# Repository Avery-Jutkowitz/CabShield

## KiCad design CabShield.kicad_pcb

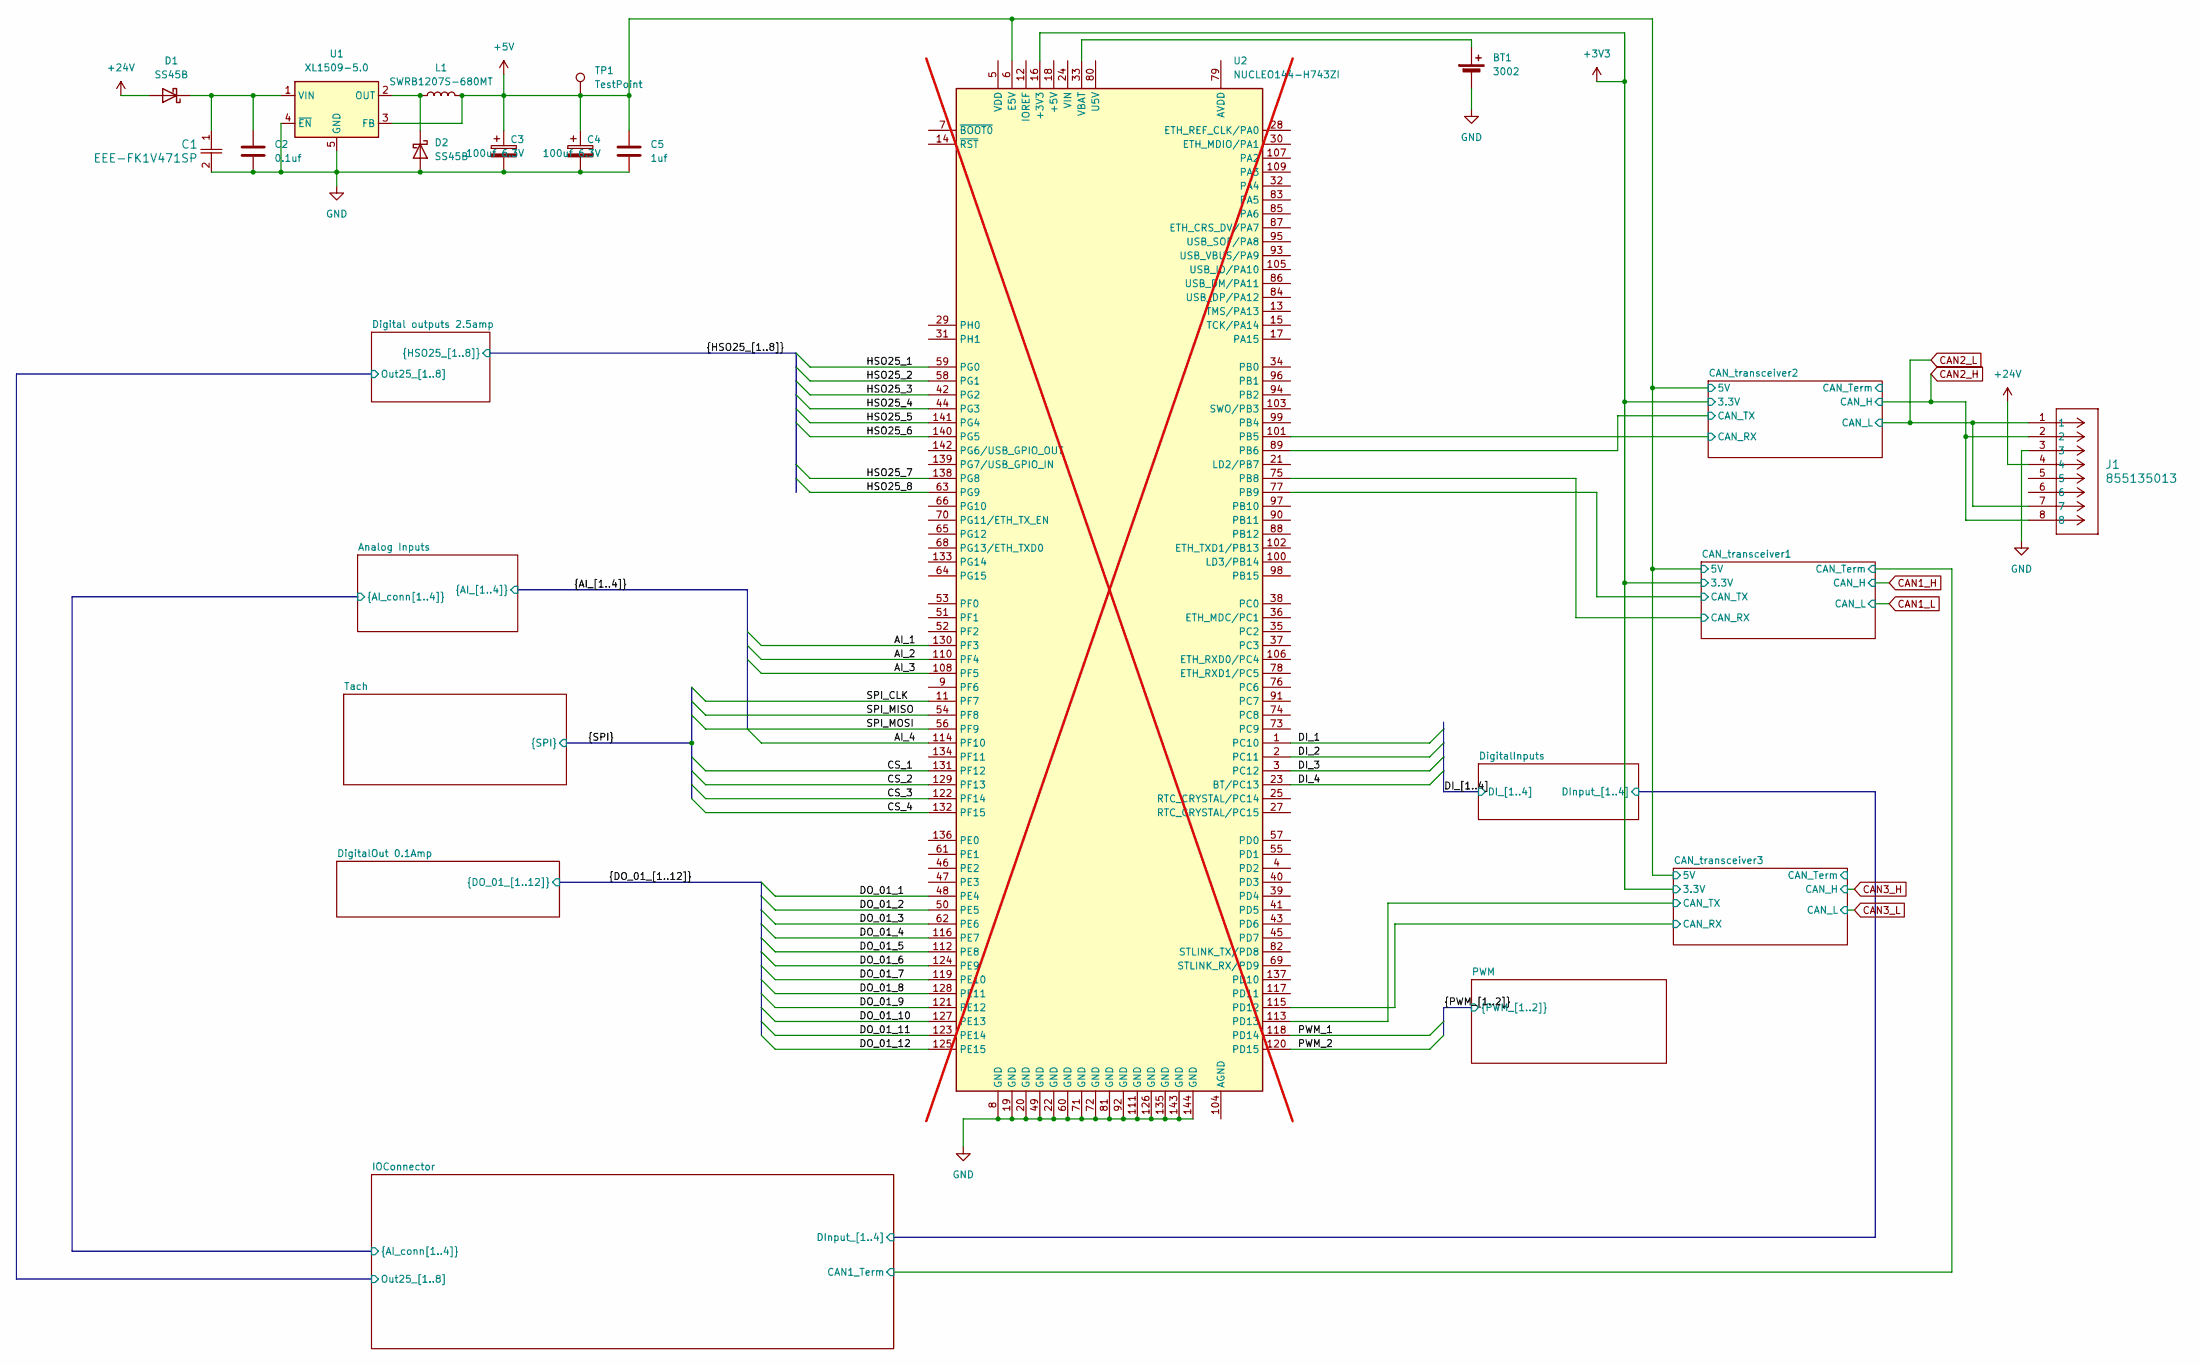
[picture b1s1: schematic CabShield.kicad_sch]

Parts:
BT1: 3002; BatteryHolder_Keystone_3002_1x2032; Manufacturer_Part_Number 3002
C1: EEE-FK1V471SP; CAP_FKS_G_PAN; Manufacturer_Part_Number EEE-FK1V471SP
C2: 0.1uf; C_0603_1608Metric; Manufacturer_Part_Number 0603B104K500XD
C3, C4: 100uf 6.3V; C_1210_3225Metric; Manufacturer_Part_Number TAJB107K006RNJ
C5: 1uf; C_0603_1608Metric; Manufacturer_Part_Number 0603B105K500XD
D1, D2: SS45B; D_SMB; Manufacturer_Part_Number SS45B
J1: 855135013; CONN_85513-5013_MOL; Manufacturer_Part_Number 855135013
L1: SWRB1207S-680MT; L_Sunlord_SWRB1204S; Manufacturer_Part_Number SWRB1207S-680MT
TP1: TestPoint; TestPoint_Pad_1.5x1.5mm
U1: XL1509-5.0; SOIC-8_3.9x4.9mm_P1.27mm; Manufacturer_Part_Number XL1509-5.0
U2: NUCLEO144-H743ZI; ST_Morpho_Connector_144_STLink; not fitted

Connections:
+3V3: U2.16 (+3V3); also elsewhere on the board
+5V: C3.1, C4.1, C5.1, L1.2, TP1.1, U1.3 (FB), U2.6 (E5V); also elsewhere on the board
+24V: D1.2 (A), J1.4; also elsewhere on the board
/AI_1: U2.130 (PF3); also elsewhere on the board
/AI_2: U2.110 (PF4); also elsewhere on the board
/AI_3: U2.108 (PF5); also elsewhere on the board
/AI_4: U2.114 (PF10); also elsewhere on the board
/CAN_transceiver1/CAN_RX: U2.75 (PB8); also elsewhere on the board
/CAN_transceiver1/CAN_TX: U2.77 (PB9); also elsewhere on the board
/CAN_transceiver2/CAN_H: J1.2, J1.8; also elsewhere on the board
/CAN_transceiver2/CAN_L: J1.1, J1.7; also elsewhere on the board
/CAN_transceiver2/CAN_RX: U2.101 (PB5); also elsewhere on the board
/CAN_transceiver2/CAN_TX: U2.89 (PB6); also elsewhere on the board
/CS_1: U2.131 (PF12); also elsewhere on the board
/CS_2: U2.129 (PF13); also elsewhere on the board
/CS_3: U2.122 (PF14); also elsewhere on the board
/CS_4: U2.132 (PF15); also elsewhere on the board
/DI_1: U2.1 (PC10); also elsewhere on the board
/DI_2: U2.2 (PC11); also elsewhere on the board
/DI_3: U2.3 (PC12); also elsewhere on the board
/DI_4: U2.23 (BT/PC13); also elsewhere on the board
/DO_01_1: U2.48 (PE4); also elsewhere on the board
/DO_01_2: U2.50 (PE5); also elsewhere on the board
/DO_01_3: U2.62 (PE6); also elsewhere on the board
/DO_01_4: U2.116 (PE7); also elsewhere on the board
/DO_01_5: U2.112 (PE8); also elsewhere on the board
/DO_01_6: U2.124 (PE9); also elsewhere on the board
/DO_01_7: U2.119 (PE10); also elsewhere on the board
/DO_01_8: U2.128 (PE11); also elsewhere on the board
/DO_01_9: U2.121 (PE12); also elsewhere on the board
/DO_01_10: U2.127 (PE13); also elsewhere on the board
/DO_01_11: U2.123 (PE14); also elsewhere on the board
/DO_01_12: U2.125 (PE15); also elsewhere on the board
/HSO25_1: U2.59 (PG0); also elsewhere on the board
/HSO25_2: U2.58 (PG1); also elsewhere on the board
/HSO25_3: U2.42 (PG2); also elsewhere on the board
/HSO25_4: U2.44 (PG3); also elsewhere on the board
/HSO25_5: U2.141 (PG4); also elsewhere on the board
/HSO25_6: U2.140 (PG5); also elsewhere on the board
/HSO25_7: U2.138 (PG8); also elsewhere on the board
/HSO25_8: U2.63 (PG9); also elsewhere on the board
/PWM_1: U2.118 (PD14); also elsewhere on the board
/PWM_2: U2.120 (PD15); also elsewhere on the board
/SPI_CLK: U2.11 (PF7); also elsewhere on the board
/SPI_MISO: U2.54 (PF8); also elsewhere on the board
/SPI_MOSI: U2.56 (PF9); also elsewhere on the board
GND: BT1.2 (-), C1.2, C2.2, C3.2, C4.2, C5.2, D2.2 (A), J1.3, U1.4 (~EN), U1.5 (GND), U1.6 (GND), U1.7 (GND), U1.8 (GND), U2.8 (GND), U2.19 (GND), U2.20 (GND), U2.22 (GND), U2.49 (GND), U2.60 (GND), U2.71 (GND), U2.72 (GND), U2.81 (GND), U2.92 (GND), U2.111 (GND), U2.126 (GND), U2.135 (GND), U2.143 (GND), U2.144 (GND); also elsewhere on the board
unnamed: BT1.1 (+), U2.33 (VBAT)
unnamed: C1.1, C2.1, D1.1 (K), U1.1 (VIN)
unnamed: D2.1 (K), L1.1, U1.2 (OUT)

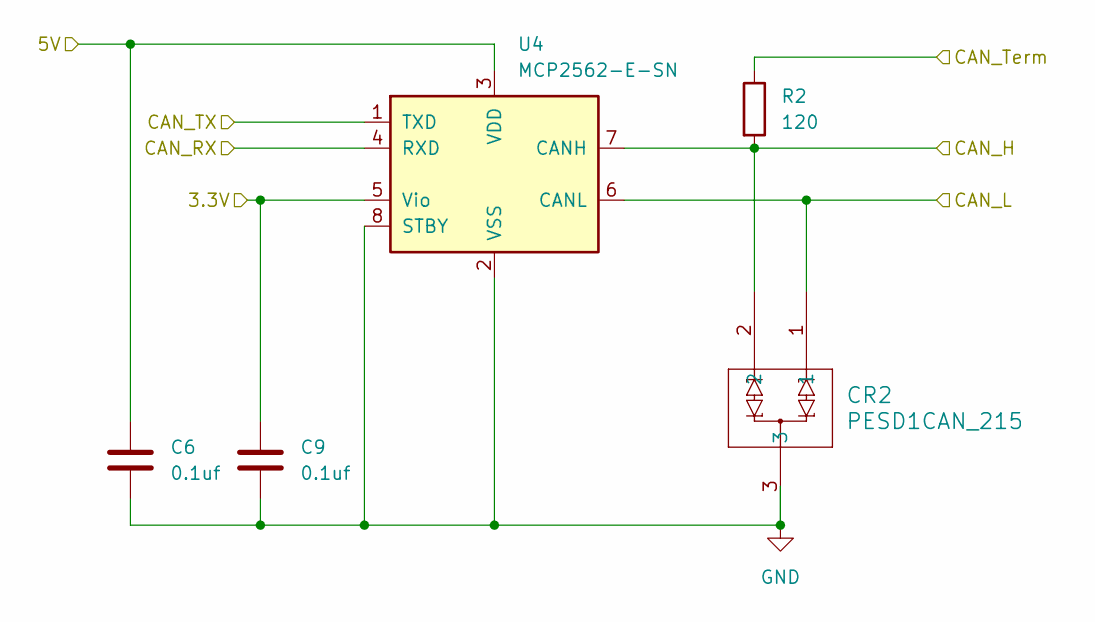
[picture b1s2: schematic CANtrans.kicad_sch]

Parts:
C6, C9: 0.1uf; C_0603_1608Metric; Manufacturer_Part_Number 0603B104K500XD
CR2: PESD1CAN_215; SOT-23; Manufacturer_Part_Number PESD1CAN_215
R2: 120; R_0603_1608Metric_Pad0.98x0.95mm_HandSolder; Manufacturer_Part_Number ERJ-3EKF1200V
U4: MCP2562-E-SN; SOIC-8_3.9x4.9mm_P1.27mm; Manufacturer_Part_Number MCP2562-E-SN

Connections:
+3V3: C9.1, U4.5 (Vio); also elsewhere on the board
+5V: C6.1, U4.3 (VDD); also elsewhere on the board
/CAN_transceiver2/CAN_H: CR2.2, R2.2, U4.7 (CANH); also elsewhere on the board
/CAN_transceiver2/CAN_L: CR2.1, U4.6 (CANL); also elsewhere on the board
/CAN_transceiver2/CAN_RX: U4.4 (RXD); also elsewhere on the board
/CAN_transceiver2/CAN_TX: U4.1 (TXD); also elsewhere on the board
/CAN_transceiver2/CAN_Term: R2.1
GND: C6.2, C9.2, CR2.3, U4.2 (VSS), U4.8 (STBY); also elsewhere on the board

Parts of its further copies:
C7, C8: 0.1uf; C_0603_1608Metric; Manufacturer_Part_Number 0603B104K500XD
CR1: PESD1CAN_215; SOT-23; Manufacturer_Part_Number PESD1CAN_215
R1: 120; R_0603_1608Metric_Pad0.98x0.95mm_HandSolder; Manufacturer_Part_Number ERJ-3EKF1200V
U3: MCP2562-E-SN; SOIC-8_3.9x4.9mm_P1.27mm; Manufacturer_Part_Number MCP2562-E-SN

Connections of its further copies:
+3V3: C7.1, U3.5 (Vio); also elsewhere on the board
+5V: C8.1, U3.3 (VDD); also elsewhere on the board
/CAN_transceiver1/CAN_RX: U3.4 (RXD); also elsewhere on the board
/CAN_transceiver1/CAN_TX: U3.1 (TXD); also elsewhere on the board
/CAN_transceiver1/CAN_Term: R1.1; also elsewhere on the board
GND: C7.2, C8.2, CR1.3, U3.2 (VSS), U3.8 (STBY); also elsewhere on the board

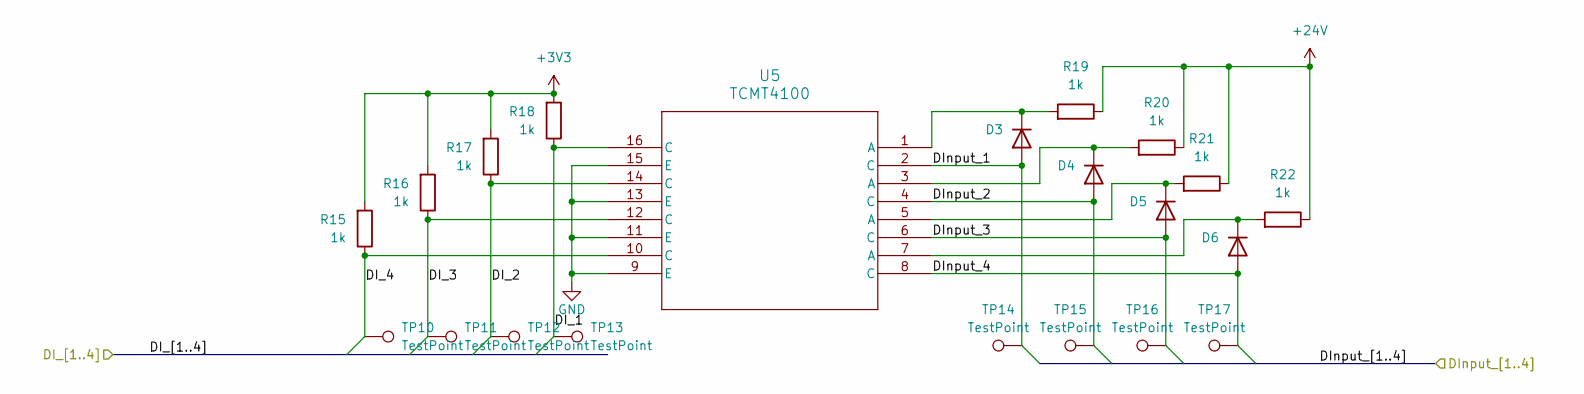
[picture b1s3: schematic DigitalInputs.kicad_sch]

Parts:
D3, D4, D5, D6: MMSZ5222BT1G; D_SOD-123; Manufacturer_Part_Number MMSZ5222BT1G
R15, R16, R17, R18, R19, R20, R21, R22: 1k; R_0402_1005Metric_Pad0.72x0.64mm_HandSolder; Manufacturer_Part_Number ERJ-2GEJ102X
TP10, TP11, TP12, TP13, TP14, TP15, TP16, TP17: TestPoint; TestPoint_Pad_1.5x1.5mm
U5: TCMT4100; SOP-16_TCMT_VIS; Manufacturer_Part_Number TCMT4100

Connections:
+3V3: R15.2, R16.2, R17.2, R18.2; also elsewhere on the board
+24V: R19.1, R20.1, R21.1, R22.1; also elsewhere on the board
/DI_1: R18.1, TP13.1, U5.16 (C); also elsewhere on the board
/DI_2: R17.1, TP12.1, U5.14 (C); also elsewhere on the board
/DI_3: R16.1, TP11.1, U5.12 (C); also elsewhere on the board
/DI_4: R15.1, TP10.1, U5.10 (C); also elsewhere on the board
/DigitalInputs/DInput_1: D3.2 (A), TP14.1, U5.2 (C); also elsewhere on the board
/DigitalInputs/DInput_2: D4.2 (A), TP15.1, U5.4 (C); also elsewhere on the board
/DigitalInputs/DInput_3: D5.2 (A), TP16.1, U5.6 (C); also elsewhere on the board
/DigitalInputs/DInput_4: D6.2 (A), TP17.1, U5.8 (C); also elsewhere on the board
GND: U5.9 (E), U5.11 (E), U5.13 (E), U5.15 (E); also elsewhere on the board
unnamed: D3.1 (K), R19.2, U5.1 (A)
unnamed: D4.1 (K), R20.2, U5.3 (A)
unnamed: D5.1 (K), R21.2, U5.5 (A)
unnamed: D6.1 (K), R22.2, U5.7 (A)

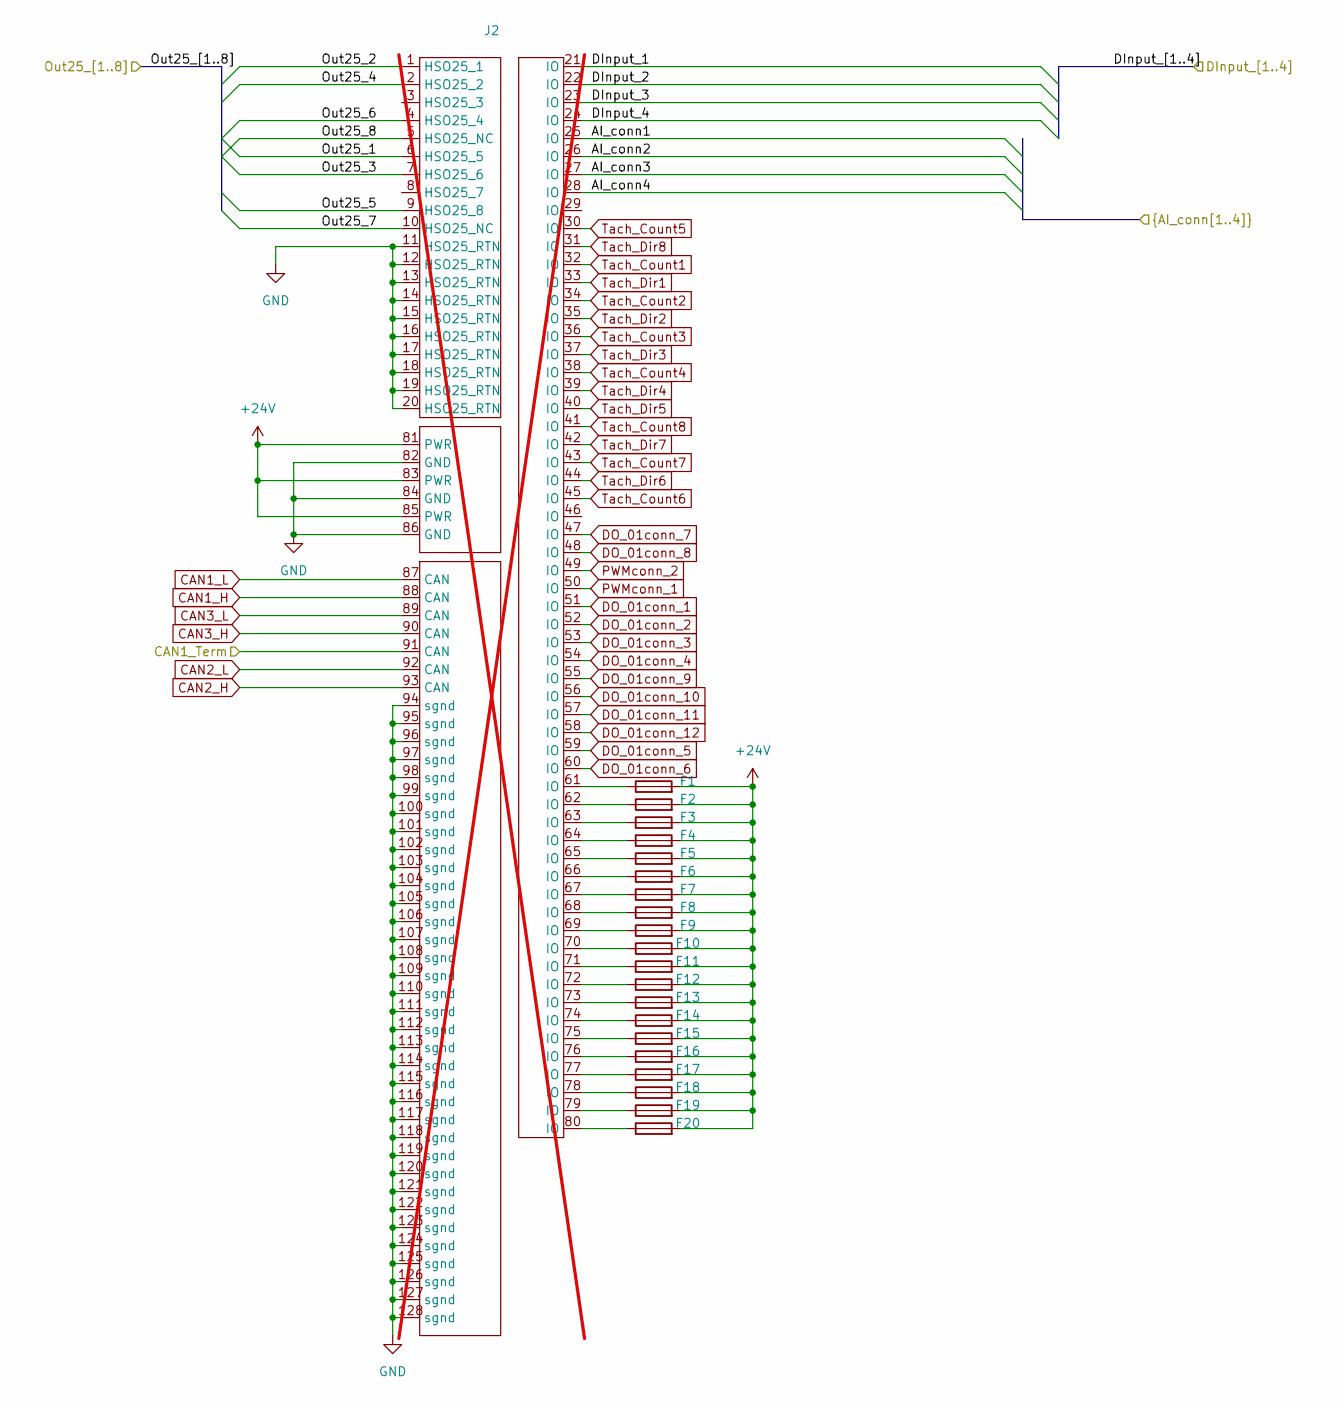
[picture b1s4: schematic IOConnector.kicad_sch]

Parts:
F1, F2, F3, F4, F5, F6, F7, F8, F9, F10, F11, F12, F13, F14, F15, F16, F17, F18, F19, F20: MF-MSMF030; Fuse_2920_7451Metric_Pad2.10x5.45mm_HandSolder; Manufacturer_Part_Number MF-MSMF030
J2: Compactus128; not fitted

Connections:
+24V: F1.2, F2.2, F3.2, F4.2, F5.2, F6.2, F7.2, F8.2, F9.2, F10.2, F11.2, F12.2, F13.2, F14.2, F15.2, F16.2, F17.2, F18.2, F19.2, F20.2, J2.81 (PWR), J2.83 (PWR), J2.85 (PWR); also elsewhere on the board
/Analog Inputs/AI_conn1: J2.25 (IO); also elsewhere on the board
/Analog Inputs/AI_conn2: J2.26 (IO); also elsewhere on the board
/Analog Inputs/AI_conn3: J2.27 (IO); also elsewhere on the board
/Analog Inputs/AI_conn4: J2.28 (IO); also elsewhere on the board
/CAN_transceiver1/CAN_Term: J2.91 (CAN); also elsewhere on the board
/CAN_transceiver2/CAN_H: J2.93 (CAN); also elsewhere on the board
/CAN_transceiver2/CAN_L: J2.92 (CAN); also elsewhere on the board
/DigitalInputs/DInput_1: J2.21 (IO); also elsewhere on the board
/DigitalInputs/DInput_2: J2.22 (IO); also elsewhere on the board
/DigitalInputs/DInput_3: J2.23 (IO); also elsewhere on the board
/DigitalInputs/DInput_4: J2.24 (IO); also elsewhere on the board
/IOConnector/Out25_1: J2.6 (HSO25_5); also elsewhere on the board
/IOConnector/Out25_2: J2.1 (HSO25_1); also elsewhere on the board
/IOConnector/Out25_3: J2.7 (HSO25_6); also elsewhere on the board
/IOConnector/Out25_4: J2.2 (HSO25_2); also elsewhere on the board
/IOConnector/Out25_5: J2.9 (HSO25_8); also elsewhere on the board
/IOConnector/Out25_6: J2.4 (HSO25_4); also elsewhere on the board
/IOConnector/Out25_7: J2.10 (HSO25_NC); also elsewhere on the board
/IOConnector/Out25_8: J2.5 (HSO25_NC); also elsewhere on the board
DO_01conn_1: J2.51 (IO); also elsewhere on the board
DO_01conn_2: J2.52 (IO); also elsewhere on the board
DO_01conn_3: J2.53 (IO); also elsewhere on the board
DO_01conn_4: J2.54 (IO); also elsewhere on the board
DO_01conn_5: J2.59 (IO); also elsewhere on the board
DO_01conn_6: J2.60 (IO); also elsewhere on the board
DO_01conn_7: J2.47 (IO); also elsewhere on the board
DO_01conn_8: J2.48 (IO); also elsewhere on the board
DO_01conn_9: J2.55 (IO); also elsewhere on the board
DO_01conn_10: J2.56 (IO); also elsewhere on the board
DO_01conn_11: J2.57 (IO); also elsewhere on the board
DO_01conn_12: J2.58 (IO); also elsewhere on the board
GND: J2.11 (HSO25_RTN), J2.12 (HSO25_RTN), J2.13 (HSO25_RTN), J2.14 (HSO25_RTN), J2.15 (HSO25_RTN), J2.16 (HSO25_RTN), J2.17 (HSO25_RTN), J2.18 (HSO25_RTN), J2.19 (HSO25_RTN), J2.20 (HSO25_RTN), J2.82 (GND), J2.84 (GND), J2.86 (GND), J2.94 (sgnd), J2.95 (sgnd), J2.96 (sgnd), J2.97 (sgnd), J2.98 (sgnd), J2.99 (sgnd), J2.100 (sgnd), J2.101 (sgnd), J2.102 (sgnd), J2.103 (sgnd), J2.104 (sgnd), J2.105 (sgnd), J2.106 (sgnd), J2.107 (sgnd), J2.108 (sgnd), J2.109 (sgnd), J2.110 (sgnd), J2.111 (sgnd), J2.112 (sgnd), J2.113 (sgnd), J2.114 (sgnd), J2.115 (sgnd), J2.116 (sgnd), J2.117 (sgnd), J2.118 (sgnd), J2.119 (sgnd), J2.120 (sgnd), J2.121 (sgnd), J2.122 (sgnd), J2.123 (sgnd), J2.124 (sgnd), J2.125 (sgnd), J2.126 (sgnd), J2.127 (sgnd), J2.128 (sgnd); also elsewhere on the board
unnamed: F1.1, J2.61 (IO)
unnamed: F2.1, J2.62 (IO)
unnamed: F3.1, J2.63 (IO)
unnamed: F4.1, J2.64 (IO)
unnamed: F5.1, J2.65 (IO)
unnamed: F6.1, J2.66 (IO)
unnamed: F7.1, J2.67 (IO)
unnamed: F8.1, J2.68 (IO)
unnamed: F9.1, J2.69 (IO)
unnamed: F10.1, J2.70 (IO)
unnamed: F11.1, J2.71 (IO)
unnamed: F12.1, J2.72 (IO)
unnamed: F13.1, J2.73 (IO)
unnamed: F14.1, J2.74 (IO)
unnamed: F15.1, J2.75 (IO)
unnamed: F16.1, J2.76 (IO)
unnamed: F17.1, J2.77 (IO)
unnamed: F18.1, J2.78 (IO)
unnamed: F19.1, J2.79 (IO)
unnamed: F20.1, J2.80 (IO)
PWMconn_1: J2.50 (IO); also elsewhere on the board
PWMconn_2: J2.49 (IO); also elsewhere on the board
Tach_Count1: J2.32 (IO); also elsewhere on the board
Tach_Count2: J2.34 (IO); also elsewhere on the board
Tach_Count3: J2.36 (IO); also elsewhere on the board
Tach_Count4: J2.38 (IO); also elsewhere on the board
Tach_Count5: J2.30 (IO); also elsewhere on the board
Tach_Count6: J2.45 (IO); also elsewhere on the board
Tach_Count7: J2.43 (IO); also elsewhere on the board
Tach_Count8: J2.41 (IO); also elsewhere on the board
Tach_Dir1: J2.33 (IO); also elsewhere on the board
Tach_Dir2: J2.35 (IO); also elsewhere on the board
Tach_Dir3: J2.37 (IO); also elsewhere on the board
Tach_Dir4: J2.39 (IO); also elsewhere on the board
Tach_Dir5: J2.40 (IO); also elsewhere on the board
Tach_Dir6: J2.44 (IO); also elsewhere on the board
Tach_Dir7: J2.42 (IO); also elsewhere on the board
Tach_Dir8: J2.31 (IO); also elsewhere on the board

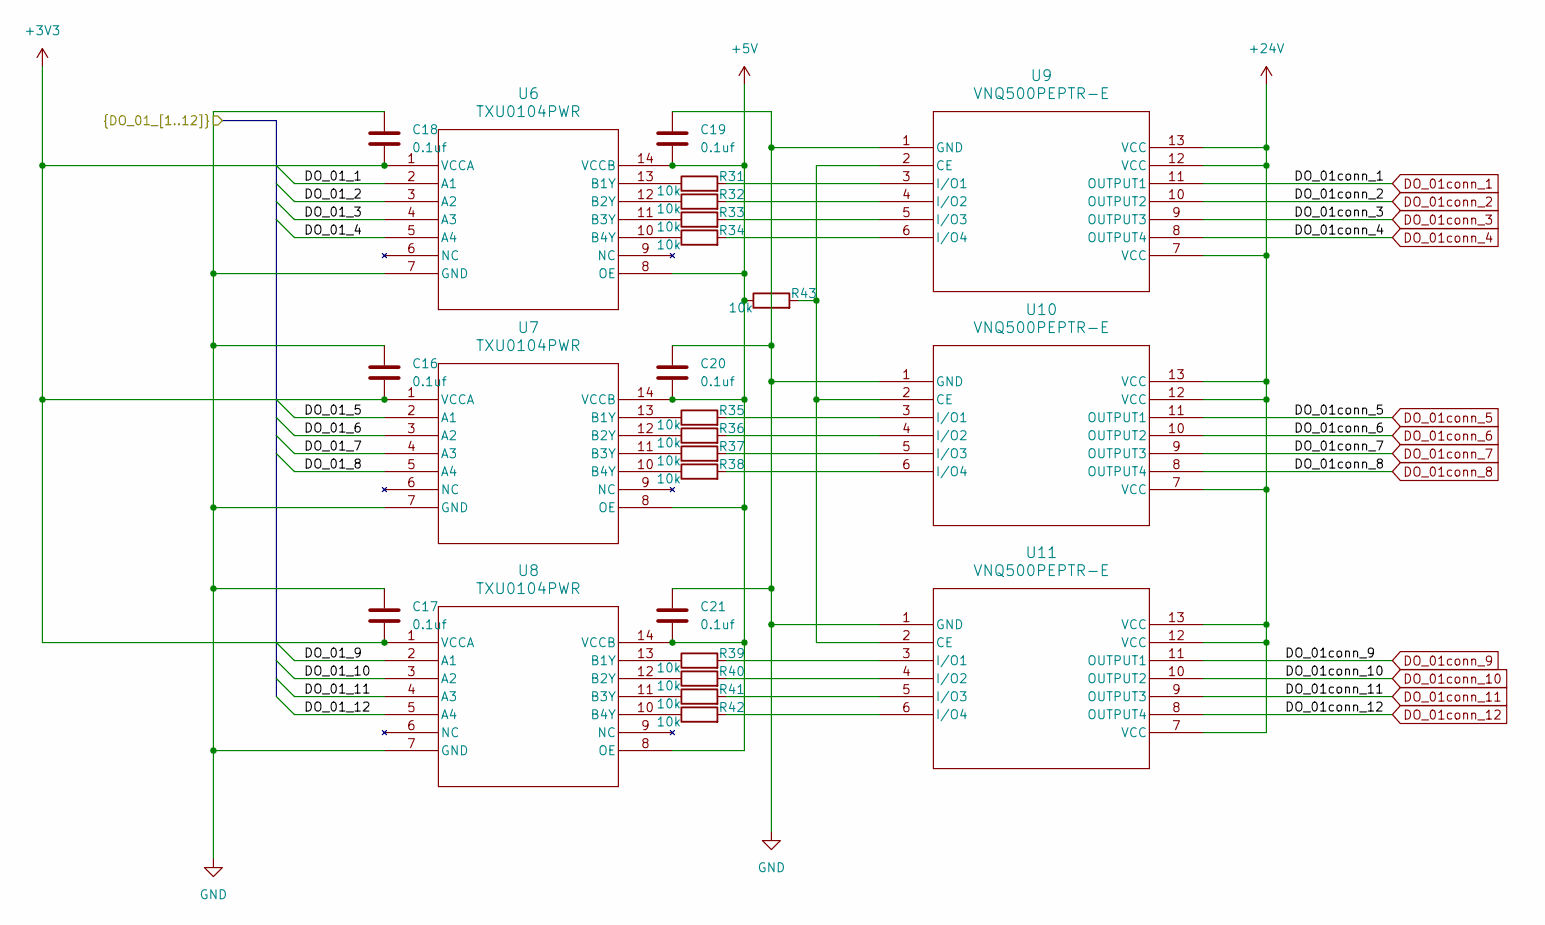
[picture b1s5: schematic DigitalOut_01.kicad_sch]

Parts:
C16, C17, C18, C19, C20, C21: 0.1uf; C_0603_1608Metric; Manufacturer_Part_Number 0603B104K500XD
R31, R32, R33, R34, R35, R36, R37, R38, R39, R40, R41, R42, R43: 10k; R_0402_1005Metric_Pad0.72x0.64mm_HandSolder; Manufacturer_Part_Number ERJ-2GEJ103X
U6, U7, U8: TXU0104PWR; TSSOP_0104PWR_TEX; Manufacturer_Part_Number TXU0104PWR
U9, U10, U11: VNQ500PEPTR-E; POWERSSO-12_STM; Manufacturer_Part_Number VNQ500PEPTR-E

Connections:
+3V3: C16.2, C17.2, C18.2, U6.1 (VCCA), U7.1 (VCCA), U8.1 (VCCA); also elsewhere on the board
+5V: C19.2, C20.2, C21.2, R43.1, U6.8 (OE), U6.14 (VCCB), U7.8 (OE), U7.14 (VCCB), U8.8 (OE), U8.14 (VCCB); also elsewhere on the board
+24V: U9.7 (VCC), U9.12 (VCC), U9.13 (VCC), U10.7 (VCC), U10.12 (VCC), U10.13 (VCC), U11.7 (VCC), U11.12 (VCC), U11.13 (VCC); also elsewhere on the board
/DO_01_1: U6.2 (A1); also elsewhere on the board
/DO_01_2: U6.3 (A2); also elsewhere on the board
/DO_01_3: U6.4 (A3); also elsewhere on the board
/DO_01_4: U6.5 (A4); also elsewhere on the board
/DO_01_5: U7.2 (A1); also elsewhere on the board
/DO_01_6: U7.3 (A2); also elsewhere on the board
/DO_01_7: U7.4 (A3); also elsewhere on the board
/DO_01_8: U7.5 (A4); also elsewhere on the board
/DO_01_9: U8.2 (A1); also elsewhere on the board
/DO_01_10: U8.3 (A2); also elsewhere on the board
/DO_01_11: U8.4 (A3); also elsewhere on the board
/DO_01_12: U8.5 (A4); also elsewhere on the board
DO_01conn_1: U9.11 (OUTPUT1); also elsewhere on the board
DO_01conn_2: U9.10 (OUTPUT2); also elsewhere on the board
DO_01conn_3: U9.9 (OUTPUT3); also elsewhere on the board
DO_01conn_4: U9.8 (OUTPUT4); also elsewhere on the board
DO_01conn_5: U10.11 (OUTPUT1); also elsewhere on the board
DO_01conn_6: U10.10 (OUTPUT2); also elsewhere on the board
DO_01conn_7: U10.9 (OUTPUT3); also elsewhere on the board
DO_01conn_8: U10.8 (OUTPUT4); also elsewhere on the board
DO_01conn_9: U11.11 (OUTPUT1); also elsewhere on the board
DO_01conn_10: U11.10 (OUTPUT2); also elsewhere on the board
DO_01conn_11: U11.9 (OUTPUT3); also elsewhere on the board
DO_01conn_12: U11.8 (OUTPUT4); also elsewhere on the board
GND: C16.1, C17.1, C18.1, C19.1, C20.1, C21.1, U6.7 (GND), U7.7 (GND), U8.7 (GND), U9.1 (GND), U10.1 (GND), U11.1 (GND); also elsewhere on the board
unnamed: R31.1, U6.13 (B1Y)
unnamed: R32.1, U6.12 (B2Y)
unnamed: R33.1, U6.11 (B3Y)
unnamed: R34.1, U6.10 (B4Y)
unnamed: R35.1, U7.13 (B1Y)
unnamed: R36.1, U7.12 (B2Y)
unnamed: R37.1, U7.11 (B3Y)
unnamed: R38.1, U7.10 (B4Y)
unnamed: R39.1, U8.13 (B1Y)
unnamed: R40.1, U8.12 (B2Y)
unnamed: R41.1, U8.11 (B3Y)
unnamed: R42.1, U8.10 (B4Y)
unnamed: R31.2, U9.3 (I/O1)
unnamed: R32.2, U9.4 (I/O2)
unnamed: R33.2, U9.5 (I/O3)
unnamed: R34.2, U9.6 (I/O4)
unnamed: R43.2, U9.2 (CE), U10.2 (CE), U11.2 (CE)
unnamed: R35.2, U10.3 (I/O1)
unnamed: R36.2, U10.4 (I/O2)
unnamed: R37.2, U10.5 (I/O3)
unnamed: R38.2, U10.6 (I/O4)
unnamed: R39.2, U11.3 (I/O1)
unnamed: R40.2, U11.4 (I/O2)
unnamed: R41.2, U11.5 (I/O3)
unnamed: R42.2, U11.6 (I/O4)

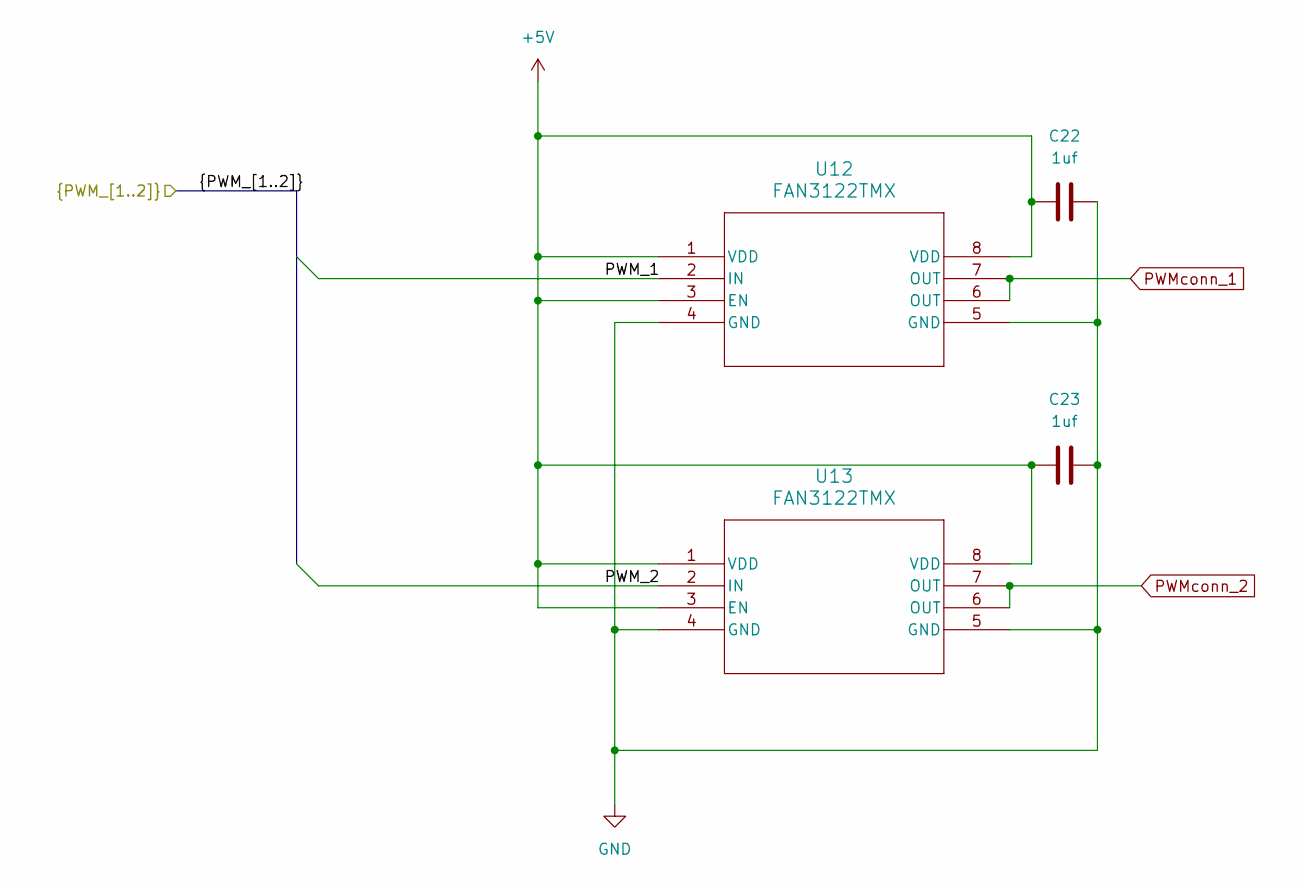
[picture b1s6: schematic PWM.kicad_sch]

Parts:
C22, C23: 1uf; C_0603_1608Metric; Manufacturer_Part_Number 0603B105K500XD
U12, U13: FAN3122TMX; SOIC8_4X5_ONS; Manufacturer_Part_Number FAN3122TMX

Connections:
+5V: C22.1, C23.1, U12.1 (VDD), U12.3 (EN), U12.8 (VDD), U13.1 (VDD), U13.3 (EN), U13.8 (VDD); also elsewhere on the board
/PWM_1: U12.2 (IN); also elsewhere on the board
/PWM_2: U13.2 (IN); also elsewhere on the board
GND: C22.2, C23.2, U12.4 (GND), U12.5 (GND), U13.4 (GND), U13.5 (GND); also elsewhere on the board
PWMconn_1: U12.6 (OUT), U12.7 (OUT); also elsewhere on the board
PWMconn_2: U13.6 (OUT), U13.7 (OUT); also elsewhere on the board

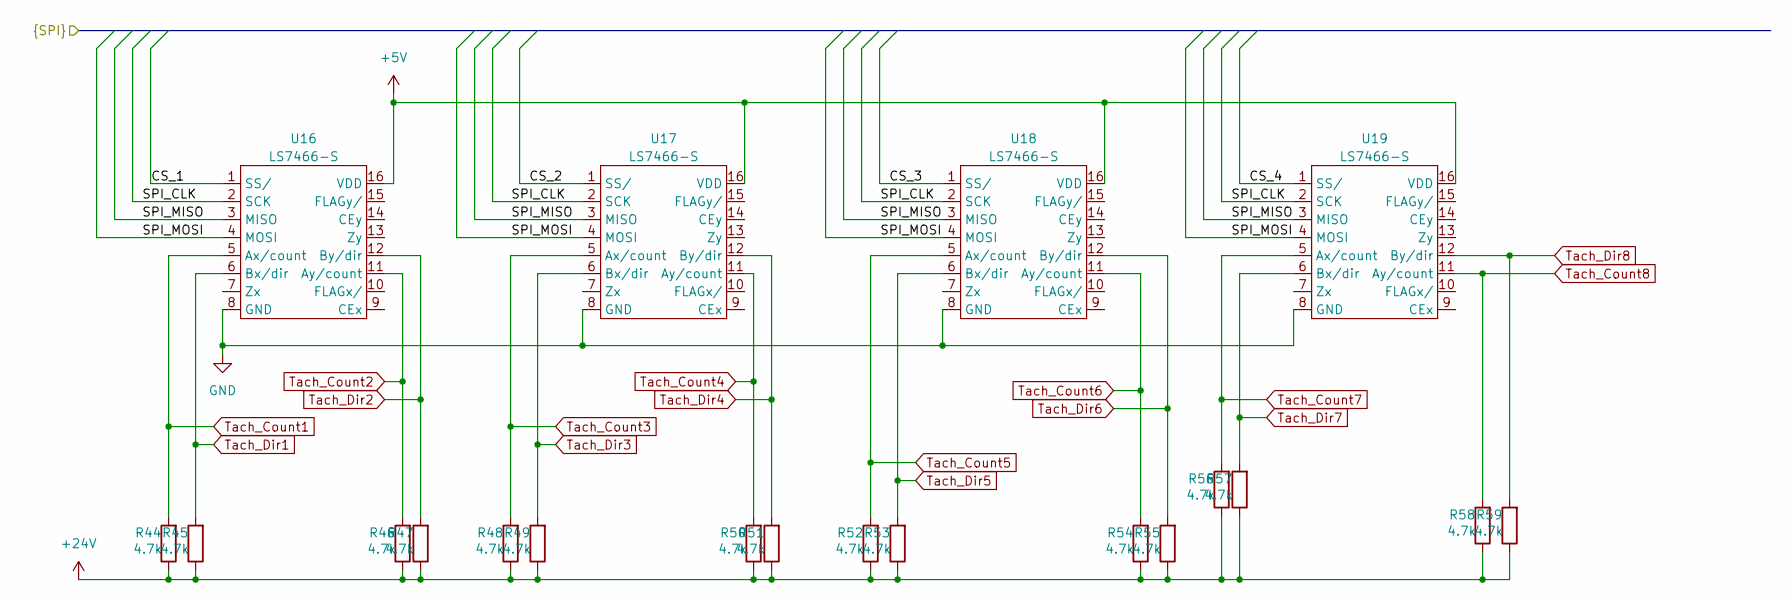
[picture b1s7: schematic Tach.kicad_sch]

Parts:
R44, R45, R46, R47, R48, R49, R50, R51, R52, R53, R54, R55, R56, R57, R58, R59: 4.7k; R_0402_1005Metric_Pad0.72x0.64mm_HandSolder; Manufacturer_Part_Number ERJ-2GEJ472X
U16, U17, U18, U19: LS7466-S; SOIC-16W_5.3x10.2mm_P1.27mm; Manufacturer_Part_Number LS7466-S

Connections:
+5V: U16.16 (VDD), U17.16 (VDD), U18.16 (VDD), U19.16 (VDD); also elsewhere on the board
+24V: R44.1, R45.1, R46.1, R47.1, R48.1, R49.1, R50.1, R51.1, R52.1, R53.1, R54.1, R55.1, R56.1, R57.1, R58.1, R59.1; also elsewhere on the board
/CS_1: U16.1 (SS/); also elsewhere on the board
/CS_2: U17.1 (SS/); also elsewhere on the board
/CS_3: U18.1 (SS/); also elsewhere on the board
/CS_4: U19.1 (SS/); also elsewhere on the board
/SPI_CLK: U16.2 (SCK), U17.2 (SCK), U18.2 (SCK), U19.2 (SCK); also elsewhere on the board
/SPI_MISO: U16.3 (MISO), U17.3 (MISO), U18.3 (MISO), U19.3 (MISO); also elsewhere on the board
/SPI_MOSI: U16.4 (MOSI), U17.4 (MOSI), U18.4 (MOSI), U19.4 (MOSI); also elsewhere on the board
GND: U16.8 (GND), U17.8 (GND), U18.8 (GND), U19.8 (GND); also elsewhere on the board
Tach_Count1: R44.2, U16.5 (Ax/count); also elsewhere on the board
Tach_Count2: R46.2, U16.11 (Ay/count); also elsewhere on the board
Tach_Count3: R48.2, U17.5 (Ax/count); also elsewhere on the board
Tach_Count4: R50.2, U17.11 (Ay/count); also elsewhere on the board
Tach_Count5: R52.2, U18.5 (Ax/count); also elsewhere on the board
Tach_Count6: R54.2, U18.11 (Ay/count); also elsewhere on the board
Tach_Count7: R56.2, U19.5 (Ax/count); also elsewhere on the board
Tach_Count8: R58.2, U19.11 (Ay/count); also elsewhere on the board
Tach_Dir1: R45.2, U16.6 (Bx/dir); also elsewhere on the board
Tach_Dir2: R47.2, U16.12 (By/dir); also elsewhere on the board
Tach_Dir3: R49.2, U17.6 (Bx/dir); also elsewhere on the board
Tach_Dir4: R51.2, U17.12 (By/dir); also elsewhere on the board
Tach_Dir5: R53.2, U18.6 (Bx/dir); also elsewhere on the board
Tach_Dir6: R55.2, U18.12 (By/dir); also elsewhere on the board
Tach_Dir7: R57.2, U19.6 (Bx/dir); also elsewhere on the board
Tach_Dir8: R59.2, U19.12 (By/dir); also elsewhere on the board

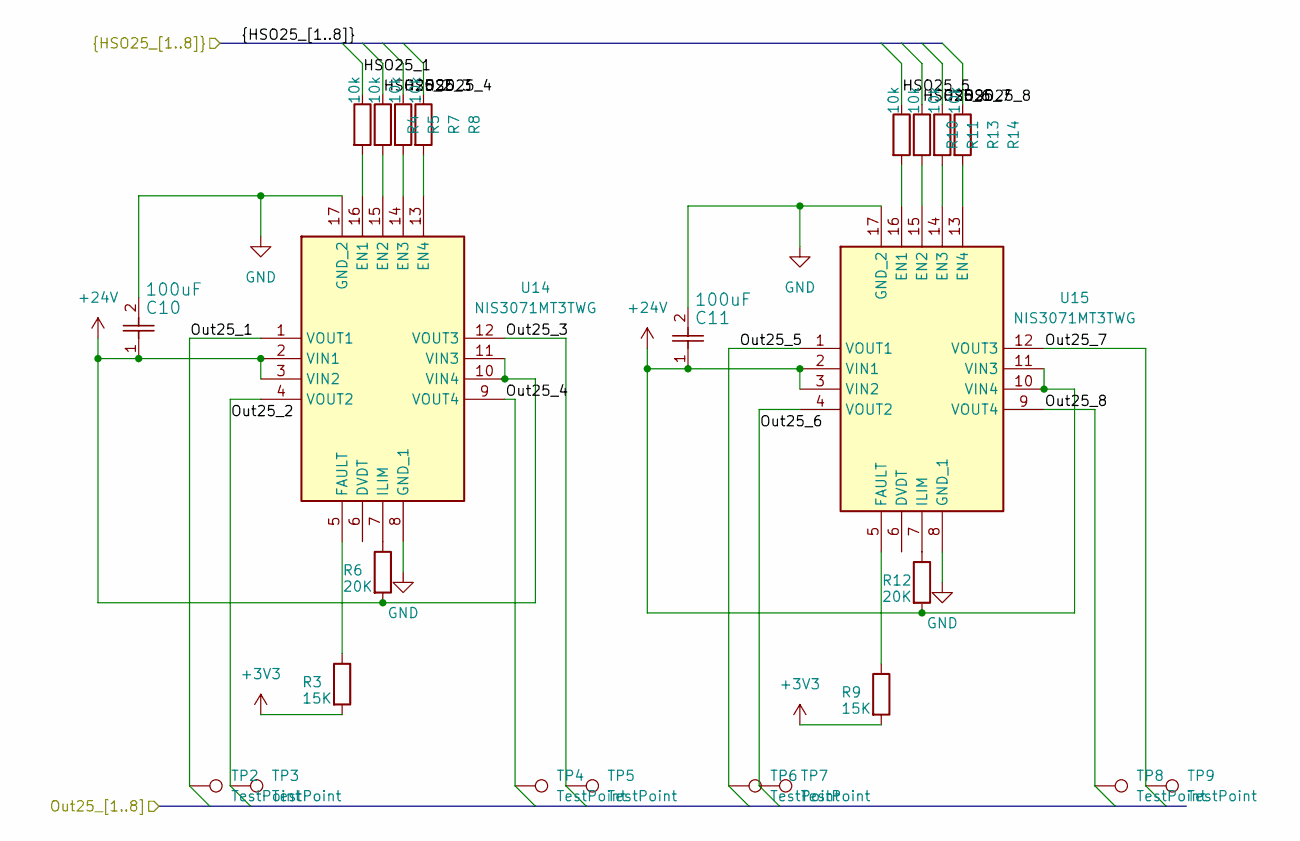
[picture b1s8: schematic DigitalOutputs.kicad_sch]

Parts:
C10, C11: 100uF; CAP_CKG57N_TDK; Manufacturer_Part_Number CKG57NX7R1V107M500JH
R3, R9: 15K; R_0402_1005Metric_Pad0.72x0.64mm_HandSolder; Manufacturer_Part_Number ERJ-2GEJ153X
R4, R5, R7, R8, R10, R11, R13, R14: 10k; R_0402_1005Metric_Pad0.72x0.64mm_HandSolder; Manufacturer_Part_Number ERJ-2GEJ103X
R6, R12: 20K; R_0402_1005Metric_Pad0.72x0.64mm_HandSolder; Manufacturer_Part_Number ERJ-2GEJ203X
TP2, TP3, TP4, TP5, TP6, TP7, TP8, TP9: TestPoint; TestPoint_Pad_1.5x1.5mm
U14, U15: NIS3071MT3TWG; QFN105P500X600X80-17N; Manufacturer_Part_Number NIS3071MT3TWG

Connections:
+3V3: R3.2, R9.2; also elsewhere on the board
+24V: C10.1, C11.1, R6.2, R12.2, U14.2 (VIN1), U14.3 (VIN2), U14.10 (VIN4), U14.11 (VIN3), U15.2 (VIN1), U15.3 (VIN2), U15.10 (VIN4), U15.11 (VIN3); also elsewhere on the board
/HSO25_1: R4.1; also elsewhere on the board
/HSO25_2: R5.1; also elsewhere on the board
/HSO25_3: R7.1; also elsewhere on the board
/HSO25_4: R8.1; also elsewhere on the board
/HSO25_5: R10.1; also elsewhere on the board
/HSO25_6: R11.1; also elsewhere on the board
/HSO25_7: R13.1; also elsewhere on the board
/HSO25_8: R14.1; also elsewhere on the board
/IOConnector/Out25_1: TP2.1, U14.1 (VOUT1); also elsewhere on the board
/IOConnector/Out25_2: TP3.1, U14.4 (VOUT2); also elsewhere on the board
/IOConnector/Out25_3: TP5.1, U14.12 (VOUT3); also elsewhere on the board
/IOConnector/Out25_4: TP4.1, U14.9 (VOUT4); also elsewhere on the board
/IOConnector/Out25_5: TP6.1, U15.1 (VOUT1); also elsewhere on the board
/IOConnector/Out25_6: TP7.1, U15.4 (VOUT2); also elsewhere on the board
/IOConnector/Out25_7: TP9.1, U15.12 (VOUT3); also elsewhere on the board
/IOConnector/Out25_8: TP8.1, U15.9 (VOUT4); also elsewhere on the board
GND: C10.2, C11.2, U14.8 (GND_1), U14.17 (GND_2), U15.8 (GND_1), U15.17 (GND_2); also elsewhere on the board
unnamed: R4.2, U14.16 (EN1)
unnamed: R5.2, U14.15 (EN2)
unnamed: R7.2, U14.14 (EN3)
unnamed: R8.2, U14.13 (EN4)
unnamed: R3.1, U14.5 (FAULT)
unnamed: R6.1, U14.7 (ILIM)
unnamed: R10.2, U15.16 (EN1)
unnamed: R11.2, U15.15 (EN2)
unnamed: R13.2, U15.14 (EN3)
unnamed: R14.2, U15.13 (EN4)
unnamed: R9.1, U15.5 (FAULT)
unnamed: R12.1, U15.7 (ILIM)
